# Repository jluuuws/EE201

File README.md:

# About Me

Hello, my name is Juliann Luu. My pronouns are she/her/hers. I am currently a junior in Electrical and Computer Engineering at 
the University of Washington Seattle.

My current classes:
1. **EE 201**: Computer Hardware Skills
2. **EE 280**: Exploring Devices
3. **EE 442**: Digital Signals and Filtering
4. **EE 492**: Electrical Engineering Leadership Seminar
5. **CSE 373**: Data Structures and Algorithms

### Hobbies

I love to consume many types of media - including, but not limited to: novels, webnovels, manga, anime, live-action TV series,
movies, etc. Currently, I am reading an English translated version of *The King's Avatar*, which is originally a Chinese webnovel.

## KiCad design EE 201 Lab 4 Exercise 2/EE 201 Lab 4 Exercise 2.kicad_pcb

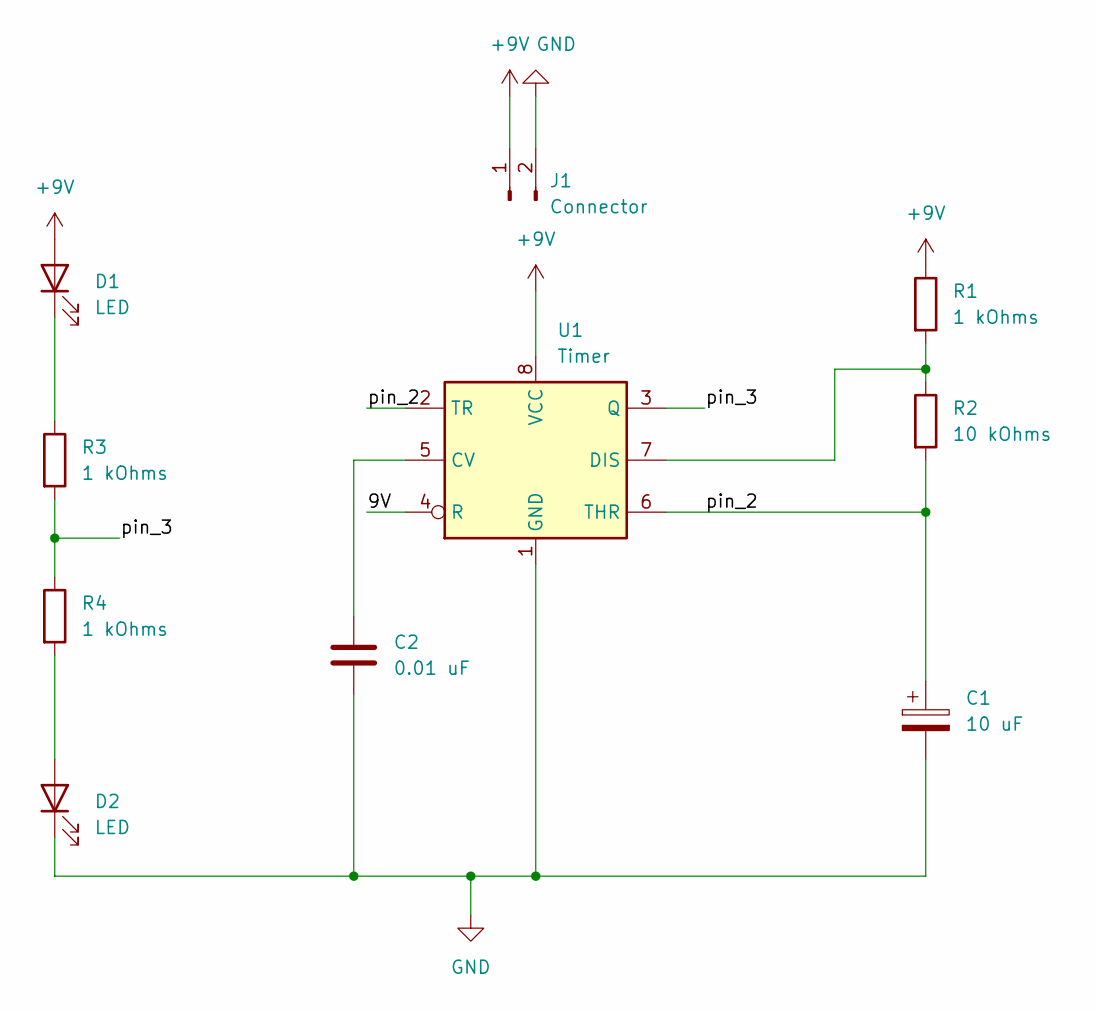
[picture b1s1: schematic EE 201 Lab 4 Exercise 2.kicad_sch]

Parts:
C1: 10 uF; CP_EIA-3216-18_Kemet-A_Pad1.58x1.35mm_HandSolder
C2: 0.01 uF; C_0805_2012Metric_Pad1.18x1.45mm_HandSolder
D1, D2: LED; LED_1206_3216Metric_Pad1.42x1.75mm_HandSolder
J1: Connector; TerminalBlock_bornier-2_P5.08mm
R1, R3, R4: 1 kOhms; R_0805_2012Metric_Pad1.20x1.40mm_HandSolder
R2: 10 kOhms; R_0805_2012Metric_Pad1.20x1.40mm_HandSolder
U1: Timer; SOIC-8-1EP_3.9x4.9mm_P1.27mm_EP2.29x3mm

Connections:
+9V: D1.2 (A), J1.1, R1.1, U1.8 (VCC)
/9V: U1.4 (R)
/pin_2: C1.1, R2.2, U1.2 (TR), U1.6 (THR)
/pin_3: R3.2, R4.1, U1.3 (Q)
GND: C1.2, C2.2, D2.1 (K), J1.2, U1.1 (GND)
unnamed: C2.1, U1.5 (CV)
unnamed: D1.1 (K), R3.1
unnamed: D2.2 (A), R4.2
unnamed: R1.2, R2.1, U1.7 (DIS)

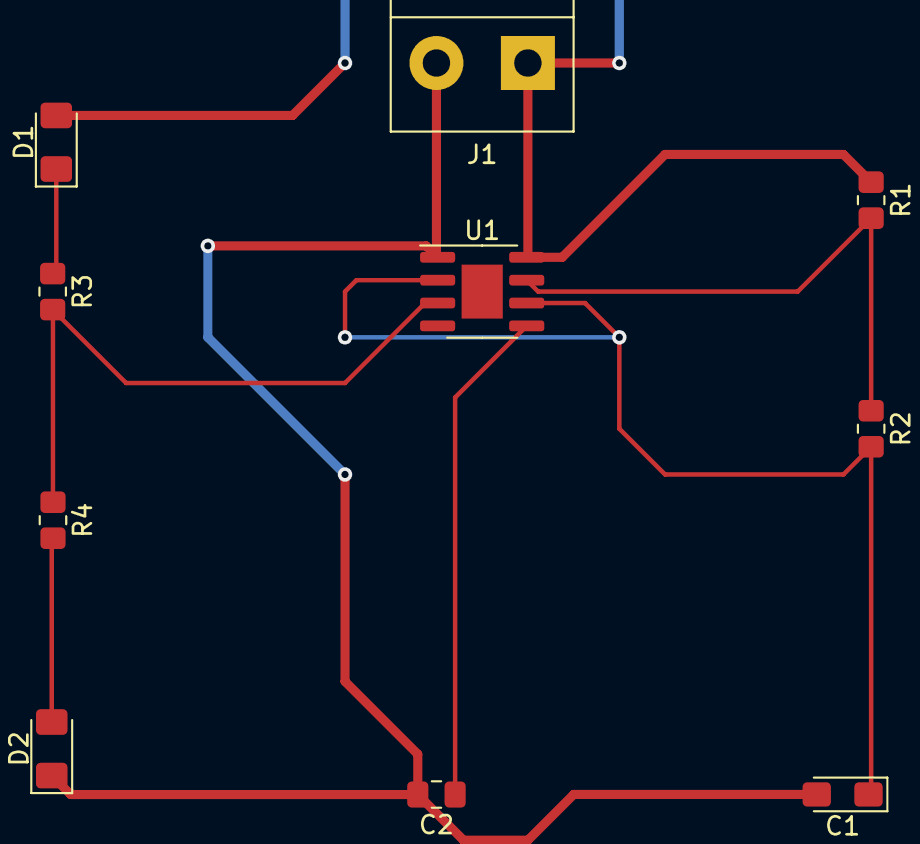
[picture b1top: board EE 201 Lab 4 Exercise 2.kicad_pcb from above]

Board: 2 copper layers, 10 parts (0 on the bottom side), 8 nets.

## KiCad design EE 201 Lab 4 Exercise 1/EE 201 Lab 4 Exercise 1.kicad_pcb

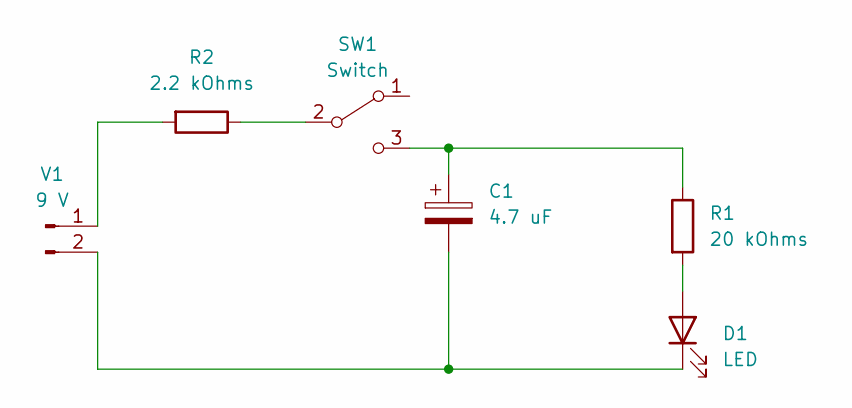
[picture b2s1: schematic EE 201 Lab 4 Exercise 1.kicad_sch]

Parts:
C1: 4.7 uF; C_Radial_D5.0mm_H5.0mm_P2.00mm
D1: LED; LED_D5.0mm
R1: 20 kOhms; R_Axial_DIN0516_L15.5mm_D5.0mm_P20.32mm_Horizontal
R2: 2.2 kOhms; R_Axial_DIN0516_L15.5mm_D5.0mm_P20.32mm_Horizontal
SW1: Switch; SW_E-Switch_EG1224_SPDT_Angled
V1: 9 V; JST_PH_B2B-PH-K_1x02_P2.00mm_Vertical

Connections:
unnamed: C1.1, R1.1, SW1.3 (C)
unnamed: C1.2, D1.1 (K), V1.2
unnamed: D1.2 (A), R1.2
unnamed: R2.1, SW1.2 (B)
unnamed: R2.2, V1.1

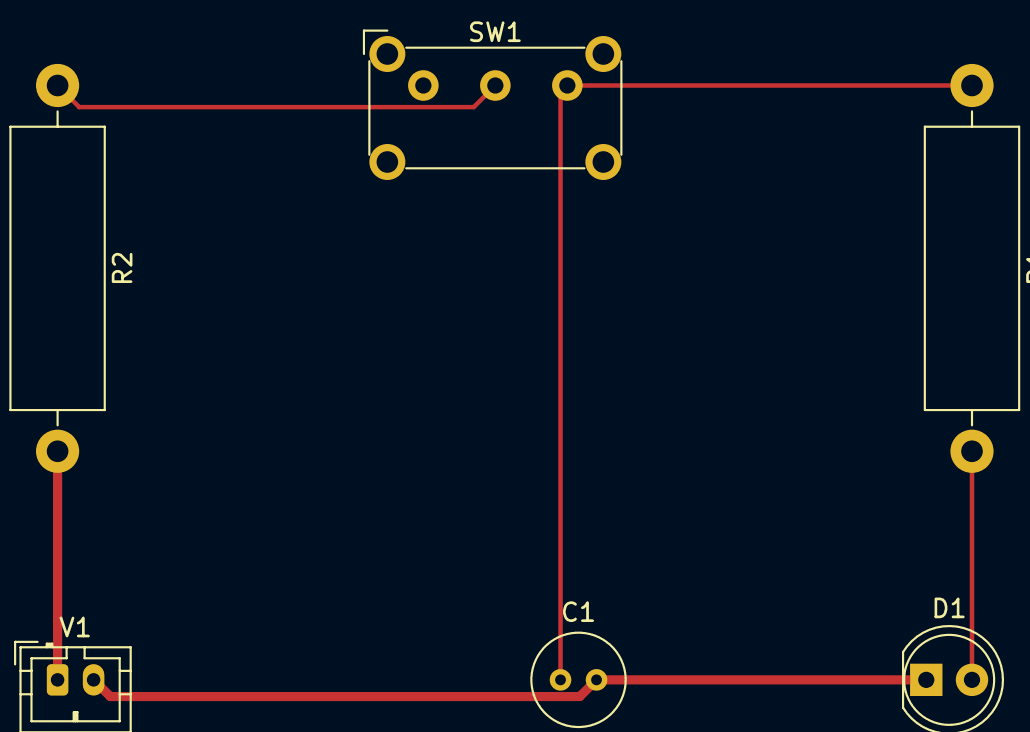
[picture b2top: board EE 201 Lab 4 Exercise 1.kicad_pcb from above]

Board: 2 copper layers, 6 parts (0 on the bottom side), 5 nets.

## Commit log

2023-01-12 2nd commit
2023-01-12 about me commit
2023-01-12 picture check
2023-01-13 finished About Me
2023-01-26 Entire Files Added for Lab 4
2023-02-03 Lab 5 commits
2023-02-09 Updated PCB Files
2023-02-16 Gerbers and Drills Zip
2023-03-02 reuploaded code (somehow didn't load last time)
2023-03-10 Pictures of Arduometer
